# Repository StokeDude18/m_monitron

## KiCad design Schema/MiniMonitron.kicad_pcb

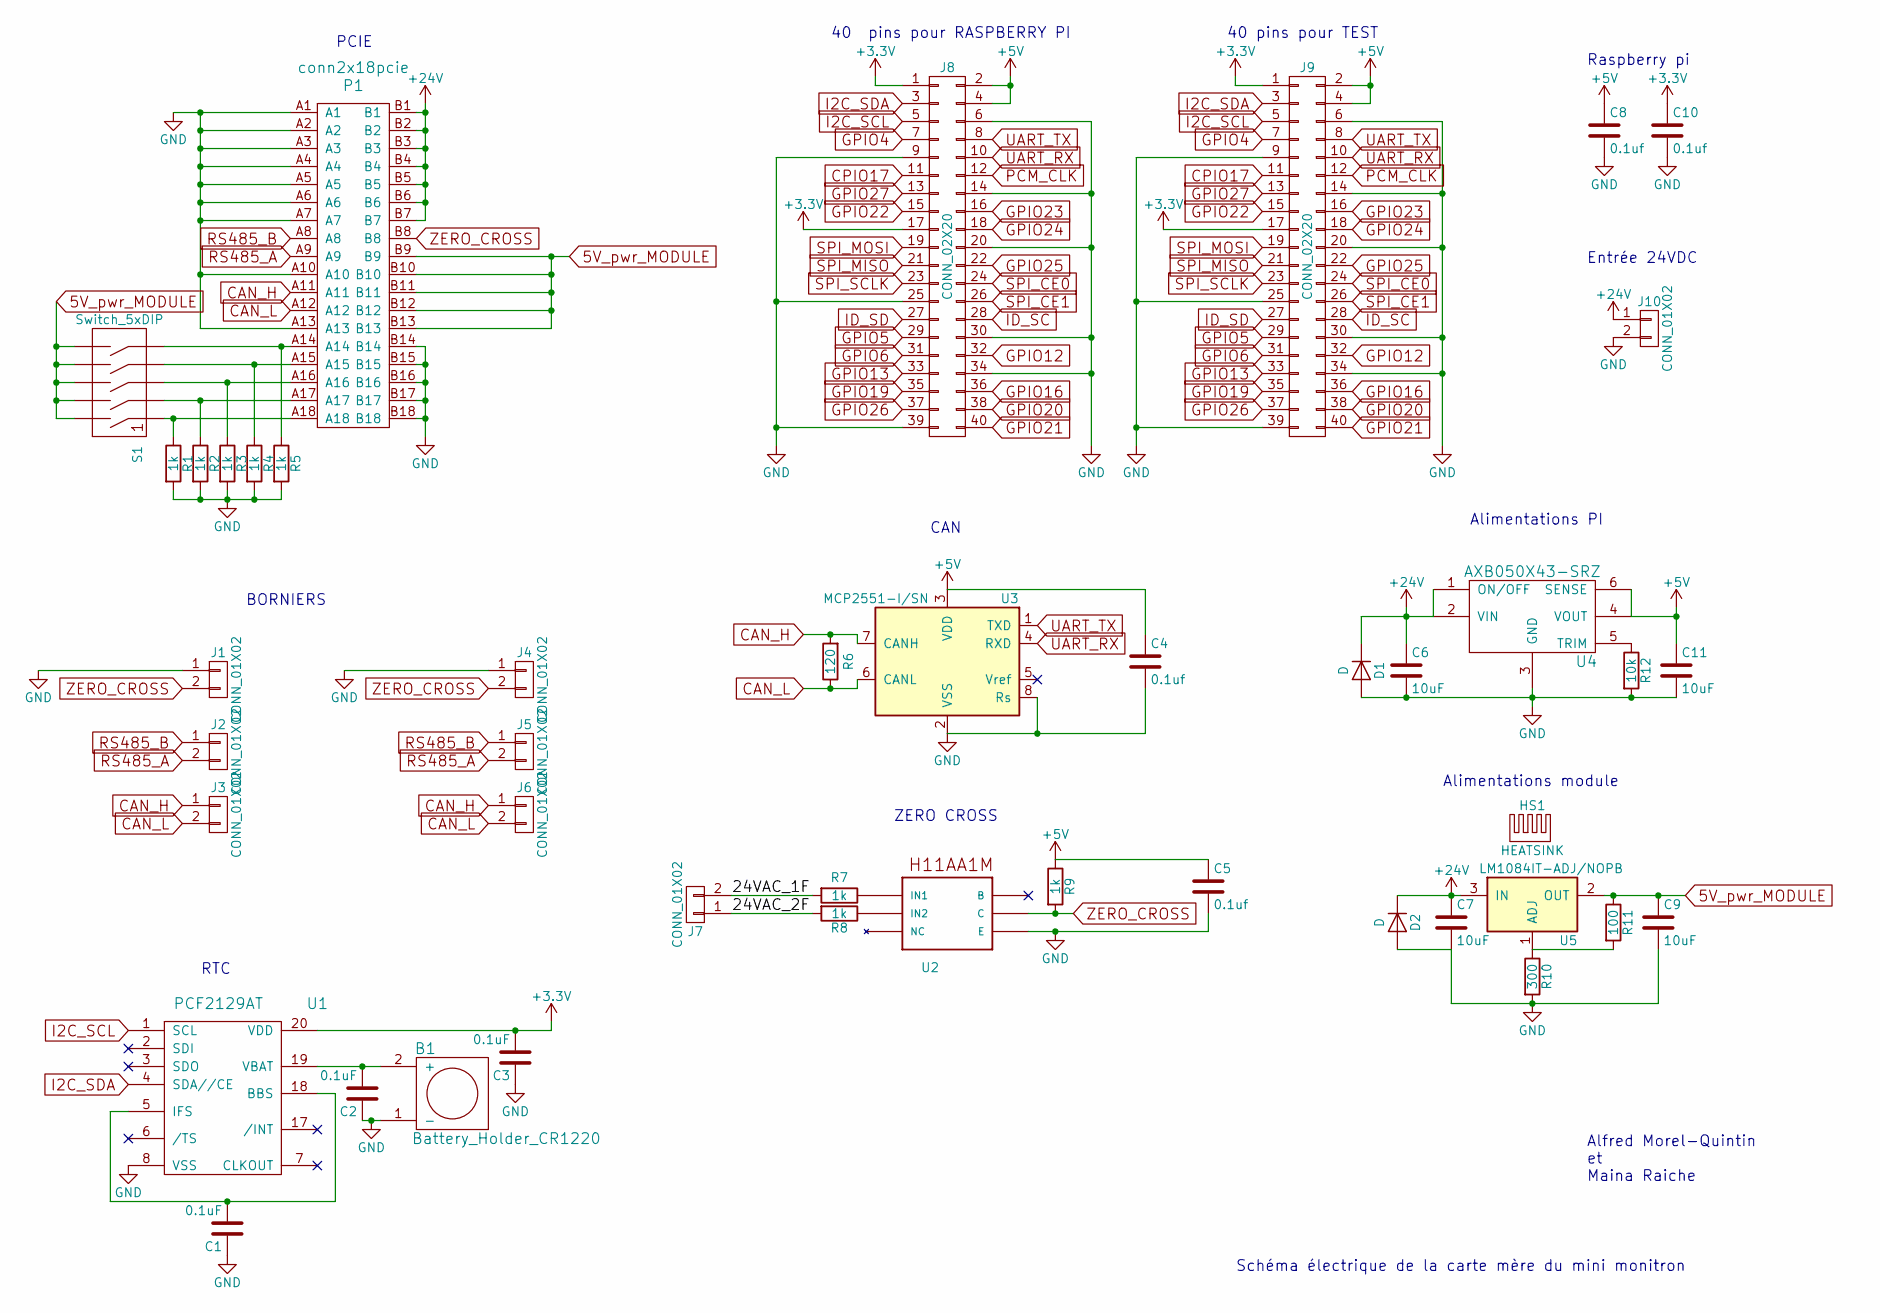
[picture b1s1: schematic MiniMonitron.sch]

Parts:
B1: Battery_Holder_CR1220; Keystone_CR1220_SMD
C1, C2, C3: 0.1uF; C_0805_HandSoldering
C4, C5, C8, C10: 0.1uf; C_0805_HandSoldering
C6, C7, C9, C11: 10uF; C_0805_HandSoldering
D1, D2: D; D_0805
HS1: HEATSINK; HeatSink_TO220_Vertical_1PP
J1, J2, J3, J4, J5, J6, J7, J10: CONN_01X02; bornier2
J8, J9: CONN_02X20; Pin_Header_Straight_2x20_Pitch2.54mm
P1: conn2x18pcie; pci-x_conn-x1_Vertical_back
R1, R2, R3, R4, R5, R7, R8, R9: 1k; R_0805_HandSoldering
R6: 120; R_0805_HandSoldering
R10: 300; R_0805_HandSoldering
R11: 100; R_0805_HandSoldering
R12: 10k; R_0805_HandSoldering
S1: Switch_5xDIP; DIP-10_W7.62mm
U1: PCF2129AT; SOIC-20W_7.5x12.8mm_Pitch1.27mm
U2: H11AA1M; DIP-6_W7.62mm
U3: MCP2551-I/SN; DIP-8_W7.62mm
U4: AXB050X43-SRZ
U5: LM1084IT-ADJ/NOPB; TO-220_Horizontal

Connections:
5V_pwr_MODULE: C9.1, P1.B9, P1.B10, P1.B11, P1.B12, P1.B13, R11.1, S1.6, S1.7, S1.8, S1.9, S1.10, U5.2 (OUT)
+3V3: C3.2, C10.1, J8.1, J8.17, J9.1, J9.17, U1.20 (VDD)
+5V: C4.1, C5.1, C8.1, C11.1, J8.2, J8.4, J9.2, J9.4, R9.1, U3.3 (VDD), U4.4 (VOUT), U4.6 (SENSE)
+24V: C6.1, C7.1, D1.1 (K), D2.1 (K), J10.1, P1.B1, P1.B2, P1.B3, P1.B4, P1.B5, P1.B6, P1.B7, U4.1 (ON/OFF), U4.2 (VIN), U5.3 (IN)
/24VAC_1F: J7.2, R7.2
/24VAC_2F: J7.1, R8.2
CAN_H: J3.1, J6.1, P1.A11, R6.2, U3.7 (CANH)
CAN_L: J3.2, J6.2, P1.A12, R6.1, U3.6 (CANL)
CPIO17: J8.11, J9.11
GND: B1.1 (-), C1.1, C2.1, C3.1, C4.2, C5.2, C6.2, C7.2, C8.2, C9.2, C10.2, C11.2, D1.2 (A), D2.2 (A), J1.1, J4.1, J8.6, J8.9, J8.14, J8.20, J8.25, J8.30, J8.34, J8.39, J9.6, J9.9, J9.14, J9.20, J9.25, J9.30, J9.34, J9.39, J10.2, P1.A1, P1.A2, P1.A3, P1.A4, P1.A5, P1.A6, P1.A7, P1.A10, P1.A13, P1.B14, P1.B15, P1.B16, P1.B17, P1.B18, R1.2, R2.2, R3.2, R4.2, R5.2, R10.2, R12.2, U1.8 (VSS), U2.4 (E), U3.2 (VSS), U3.8 (Rs), U4.3 (GND)
GPIO4: J8.7, J9.7
GPIO5: J8.29, J9.29
GPIO6: J8.31, J9.31
GPIO12: J8.32, J9.32
GPIO13: J8.33, J9.33
GPIO16: J8.36, J9.36
GPIO19: J8.35, J9.35
GPIO20: J8.38, J9.38
GPIO21: J8.40, J9.40
GPIO22: J8.15, J9.15
GPIO23: J8.16, J9.16
GPIO24: J8.18, J9.18
GPIO25: J8.22, J9.22
GPIO26: J8.37, J9.37
GPIO27: J8.13, J9.13
I2C_SCL: J8.5, J9.5, U1.1 (SCL)
I2C_SDA: J8.3, J9.3, U1.4 (SDA//CE)
ID_SC: J8.28, J9.28
ID_SD: J8.27, J9.27
unnamed: B1.2 (+), C2.2, U1.19 (VBAT)
unnamed: C1.2, U1.5 (IFS), U1.18 (BBS)
unnamed: P1.A14, R5.1, S1.5
unnamed: P1.A15, R4.1, S1.4
unnamed: P1.A16, R3.1, S1.3
unnamed: P1.A17, R2.1, S1.2
unnamed: P1.A18, R1.1, S1.1
unnamed: R7.1, U2.1 (IN1)
unnamed: R8.1, U2.2 (IN2)
unnamed: R10.1, R11.2, U5.1 (ADJ)
unnamed: R12.1, U4.5 (TRIM)
PCM_CLK: J8.12, J9.12
RS485_A: J2.2, J5.2, P1.A9
RS485_B: J2.1, J5.1, P1.A8
SPI_CE0: J8.24, J9.24
SPI_CE1: J8.26, J9.26
SPI_MISO: J8.21, J9.21
SPI_MOSI: J8.19, J9.19
SPI_SCLK: J8.23, J9.23
UART_RX: J8.10, J9.10, U3.4 (RXD)
UART_TX: J8.8, J9.8, U3.1 (TXD)
ZERO_CROSS: J1.2, J4.2, P1.B8, R9.2, U2.5 (C)

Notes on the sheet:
Raspberry pi
Schéma électrique de la carte mère du mini monitron
Alfred Morel-Quintin et Maina Raiche
40 pins pour RASPBERRY PI
40 pins pour TEST
Alimentations PI
CAN
ZERO CROSS
RTC
PCIE
BORNIERS
Entrée 24VDC
Alimentations module

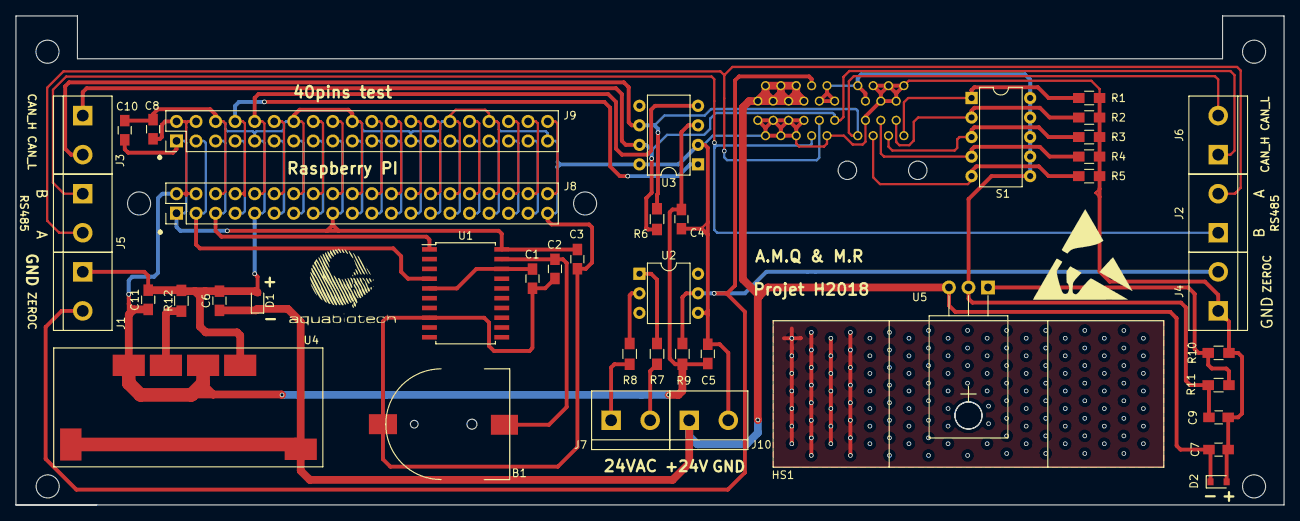
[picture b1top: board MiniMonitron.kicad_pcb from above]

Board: 2 copper layers, 164.9 x 63.6 mm, 44 parts (0 on the bottom side), 51 nets.

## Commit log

2018-01-19 premier commit avec répertoire fonctionnel
2018-01-19 Premiere version Interface
2018-01-19 SavePoint label edit
2018-01-20 Ajout deuxieme interface
2018-01-20 Ajout de la classe module
2018-01-29 Premiere version multi-fenetre compilee
2018-02-02 Fenetres d'edition pour les onglets Cycles et Lecture. Restriction d'entree dans les boites de texte
2018-02-05 Redimension des elements graphiques Ajout de toutes les fenetres d'edition de parametres
2018-02-12 Ajout du dossier du schema electrique et PCB
2018-02-12 Ajout code controle du PI
2018-02-12 Ajout dossier des fiches techniques
2018-02-12 Code compilé dans l'interface
2018-02-12 Modification du schema électrique, + ajout de fiche technique
2018-02-13 Ajout fiche technique + ajout alimentation sur schema electrique
2018-02-19 Premier affichage interface a partir de donnees recues
2018-02-19 Fonctions de lecture
2018-02-20 ajout fiches technique + finalisation schema électrique + commencement PCB
2018-02-20 Ajout de communications standardisées entre la form et le main
2018-02-23 Placement des pièces sur le PCB + commencement du routage
2018-02-25 Main et communication.h commentés
2018-02-27 Envoi simple réglé
2018-03-12 Tous les paramètres sont affichés dans l'interface
2018-03-13 PCB terminé et envoyé, fichiers gerber crées + création du dossier Documentations avec le document du manuel technique
2018-03-13 Trames d'envoi des parmètres construite
2018-03-19 Écriture SD fonctionnelle
2018-03-20 Version fonctionnelle comprenant l'édition de paramètres et l'acquisition de ceux-ci
2018-03-27 Code commenté de la première version fonctionnelle
2018-04-09 MULTI_CARTE FONCTIONNEL
2018-04-10 Correction du PCB + nouveau fichier Gerber
2018-04-13 Ajout librairie graphique (numpad)
2018-04-17 Implantation du clavier numérique fonctionnel
2018-04-17 Organisation des chiffres du numpad révisée
2018-04-26 Ménage des fichiers de build spécifiques aux systèmes utilisés pour les tests
2018-04-30 Retrait des classes graphiques des fenêtres d'édition
2018-04-30 PCB final + avancement du manuel technique
2018-04-30 Ajustements du code sans les classes graphiques
2018-04-30 Ajout de marqueurs d'édition et Séquence calibration
2018-05-08 Ajout de protection quand aucun module détecté et de détails sur le module dans le combo box de sélection du module actif
2018-05-10 Retrait d'un fichier posant problème dans le dossier BuildPi
2018-05-11 Ajustements de bugs dans le choix du mode d'opération
2018-05-11 Redimensionnement du numpad
2018-05-14 Ajout de commentaires dans les classes m_monitron_0_0, Edtiline et Numpad
2018-05-14 Complément des commentaires commencés dans le dernier commit
2018-05-15 Avancement des corrections du manuel technique + ajout photos et screenshots
2018-05-15 Ajout de détails dans la procédure d'installation et reformulation de quelques passages dans le manuel technique
2018-05-15 Reformulation d'une phrase dans la description du projet
2018-05-18 ajout d'un build sur le Pi dans /m_monitron/build-m_monitron_0_0-Desktop
2018-05-18 Ajout d'un bouton exit dans l'interface
2018-05-18 Mise en fonction du bouton exit
2018-05-18 Ajout d'un répertoire dédié aux builds pour le Pi zero
2018-05-18 Build pour Pi
2018-05-18 Ajout de la valeur en mV actuelle sur le clavier virtuel quand le mode calibration est actif
2018-05-18 retrait de la barre de titre du numpad pour libérer de l'espace
2018-05-21 Ajout des en-tête de fichiers sur tous les fichier .cpp et .h du projet
2018-05-22 Correction du bug ttyUSB0 vs serial0 dans le build du PI
2018-05-22 Ajout des unités des valeurs de lectureet réorganisation de l'onglet Control_OP
